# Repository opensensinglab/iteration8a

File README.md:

# iteration8a
iteration8a (in progress)

This is a random collection of in-progress design files and example code (written by myself or others) supporting Iteration 8a.  It's not intended for public use, but only to support my own development efforts.  Materials are not packaged for release, and any use is entirely at your own risk.

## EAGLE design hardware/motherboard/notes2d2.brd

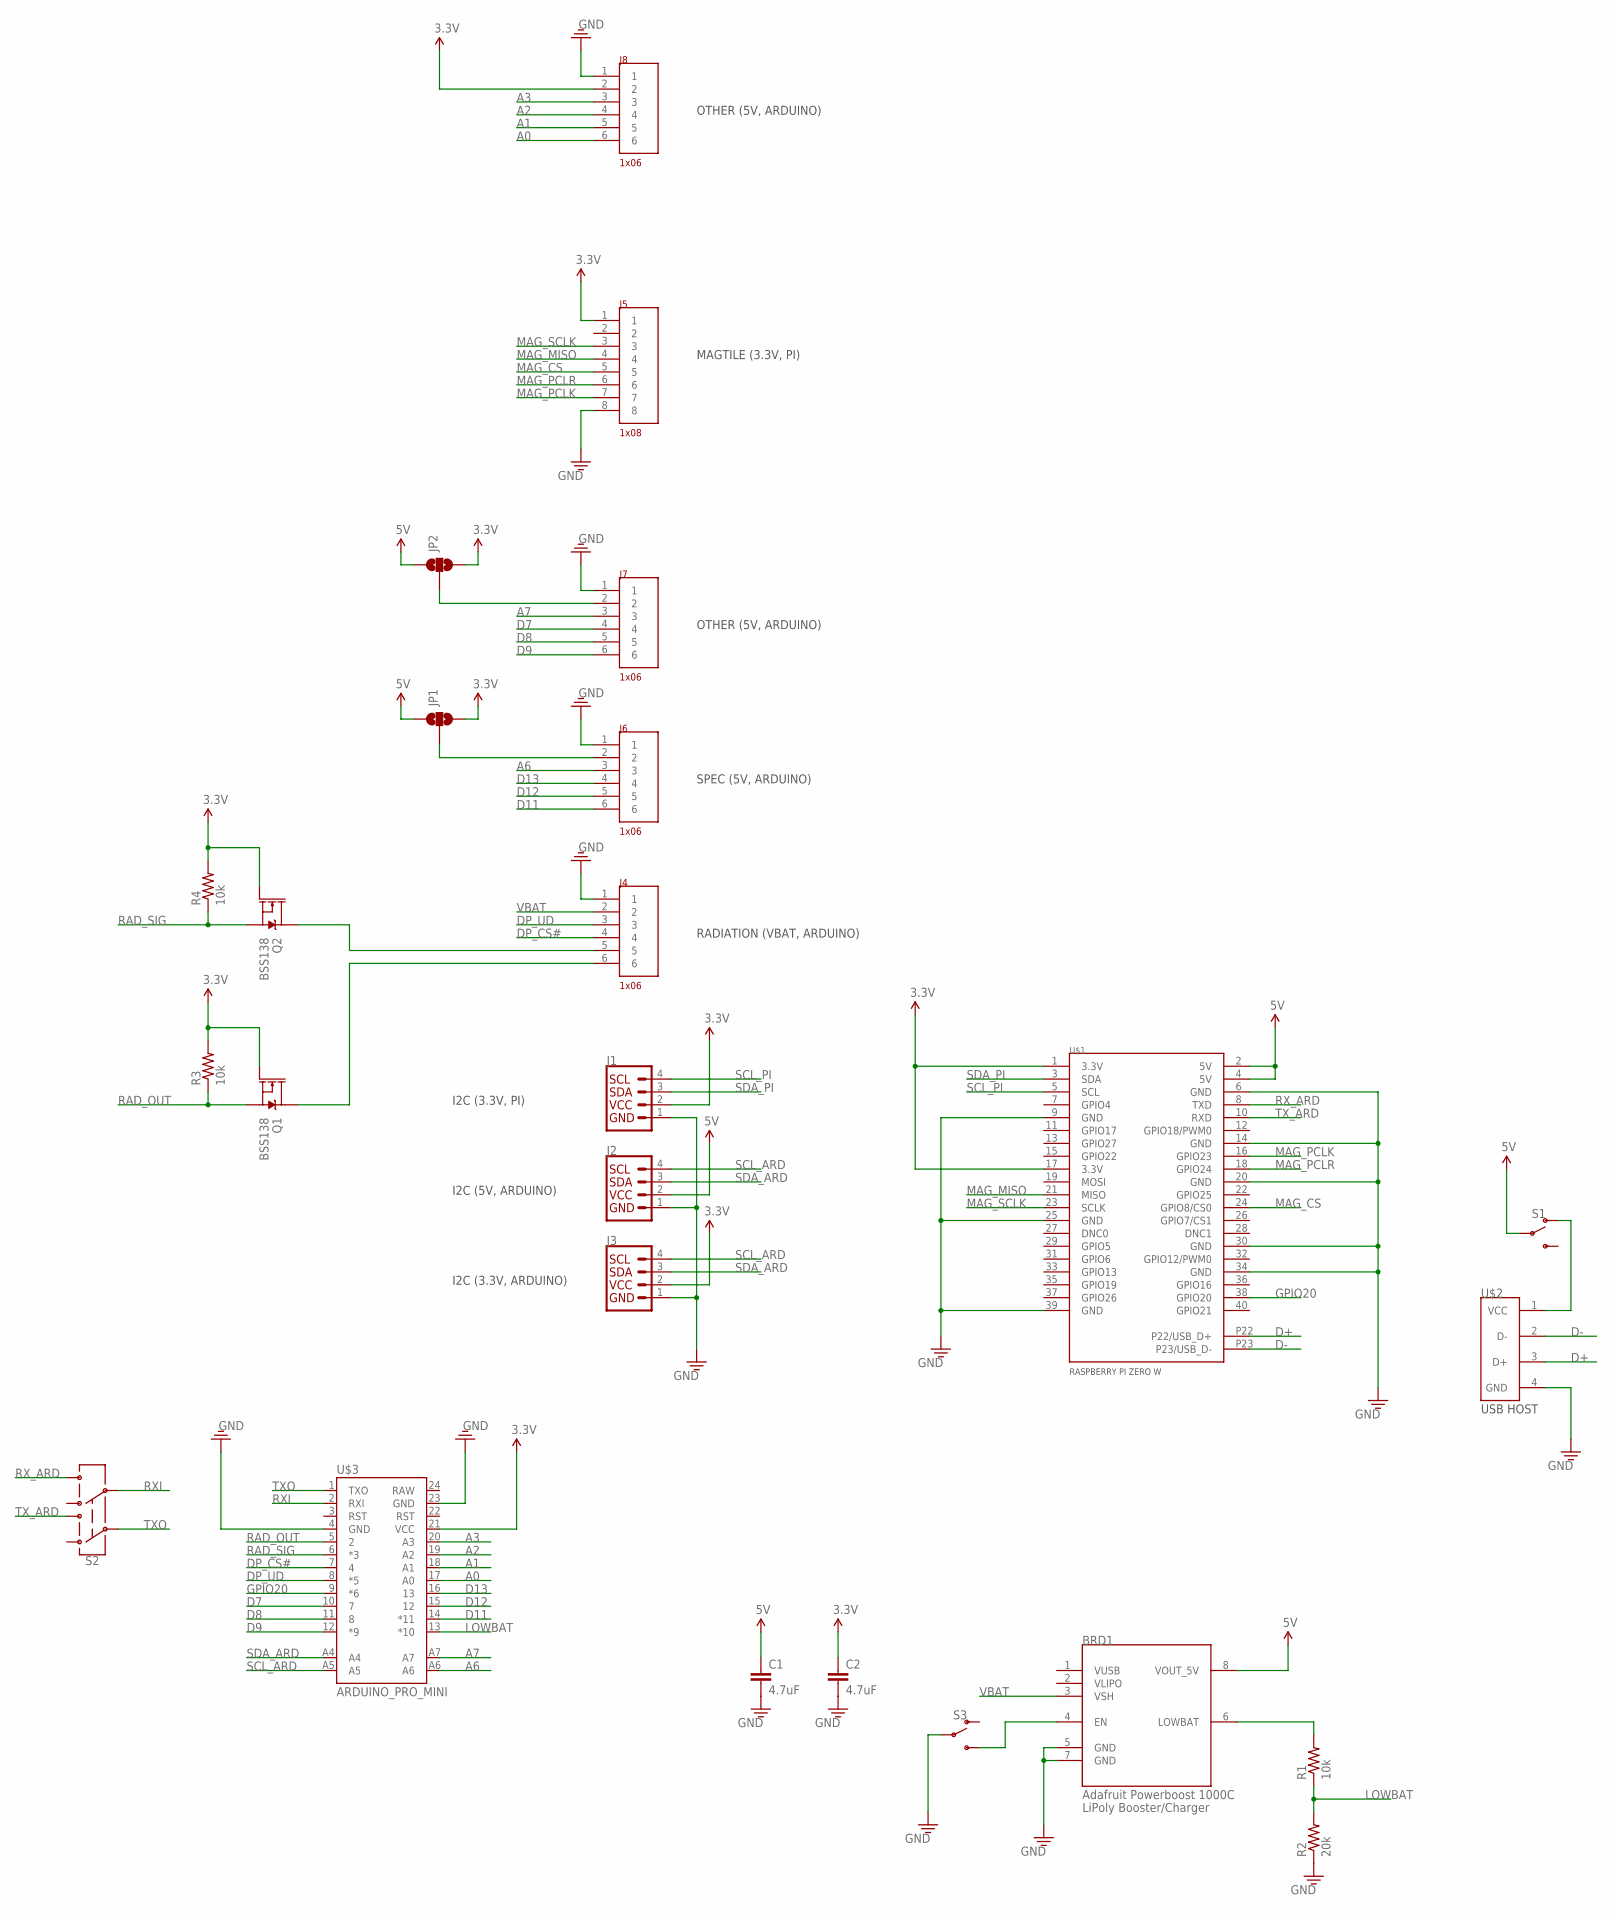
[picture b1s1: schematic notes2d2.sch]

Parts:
BRD1: ADAFRUIT_POWERBOOST_1000C
C1, C2: 4.7uF; 0603
J1, J2, J3: QWIIC_CONNECTORJS-1MM; 1X04_1MM_RA
J4, J6, J7, J8: 1X06; JST-SM06B-1MM
J5: 1X08; JST-SM08B-1MM
JP1, JP2: JUMPER-SMT_3_NO_SILK; SMT-JUMPER_3_NO_SILK
Q1, Q2: BSS138; SOT23-3
R1, R3, R4: 10k; 0603
R2: 20k; 0603
S1, S3: SWITCH-SPDT-SMD-RIGHT-ANGLE; SWITCH_SPST_SMD_A
S2: SWITCH-DPDT-SMD-AYZ0202; SWITCH_DPDT_SMD_AYZ0202
U$1: RASPBERRY-PI-ZEROW-USB
U$2: USB-HOST; 1-292303-6
U$3: ARDUINO_PRO_MINI

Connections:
3.3V: C2.1, J1.2 (VCC), J3.2 (VCC), J5.1, J8.2, JP1.3, JP2.3, Q1.1 (G), Q2.1 (G), R3.2, R4.2, U$1.1 (3.3V), U$1.17 (3.3V), U$3.21 (VCC)
5V: BRD1.8 (VOUT_5V), C1.1, J2.2 (VCC), JP1.1, JP2.1, S1.2, U$1.2 (5V), U$1.4 (5V)
A0: J8.6, U$3.17 (A0)
A1: J8.5, U$3.18 (A1)
A2: J8.4, U$3.19 (A2)
A3: J8.3, U$3.20 (A3)
A6: J6.3, U$3.A6
A7: J7.3, U$3.A7
D7: J7.4, U$3.10 (7)
D8: J7.5, U$3.11 (8)
D9: J7.6, U$3.12 (*9)
D11: J6.6, U$3.14 (*11)
D12: J6.5, U$3.15 (12)
D13: J6.4, U$3.16 (13)
D+: U$1.P22 (P22/USB_D+), U$2.3 (D+)
D-: U$1.P23 (P23/USB_D-), U$2.2 (D-)
DP_CS#: J4.4, U$3.7 (4)
DP_UD: J4.3, U$3.8 (*5)
GND: BRD1.5 (GND), BRD1.7 (GND), C1.2, C2.2, J1.1 (GND), J2.1 (GND), J3.1 (GND), J4.1, J5.8, J6.1, J7.1, J8.1, R2.1, S3.2, U$1.6 (GND), U$1.9 (GND), U$1.14 (GND), U$1.20 (GND), U$1.25 (GND), U$1.30 (GND), U$1.34 (GND), U$1.39 (GND), U$2.4 (GND), U$3.4 (GND), U$3.23 (GND)
GPIO20: U$1.38 (GPIO20), U$3.9 (*6)
LOWBAT: R1.1, R2.2, U$3.13 (*10)
MAG_CS: J5.5, U$1.24 (GPIO8/CS0)
MAG_MISO: J5.4, U$1.21 (MISO)
MAG_PCLK: J5.7, U$1.16 (GPIO23)
MAG_PCLR: J5.6, U$1.18 (GPIO24)
MAG_SCLK: J5.3, U$1.23 (SCLK)
unnamed: BRD1.4 (EN), S3.3 (S)
unnamed: J7.2, JP2.2
unnamed: J6.2, JP1.2
unnamed: J4.5, Q2.3 (D)
unnamed: J4.6, Q1.3 (D)
unnamed: BRD1.6 (LOWBAT), R1.2
unnamed: S1.1 (O), U$2.1 (VCC)
RAD_OUT: Q1.2 (S), R3.1, U$3.5 (2)
RAD_SIG: Q2.2 (S), R4.1, U$3.6 (*3)
RXI: S2.5, U$3.2 (RXI)
RX_ARD: S2.6, U$1.8 (TXD)
SCL_ARD: J2.4 (SCL), J3.4 (SCL), U$3.A5
SCL_PI: J1.4 (SCL), U$1.5 (SCL)
SDA_ARD: J2.3 (SDA), J3.3 (SDA), U$3.A4
SDA_PI: J1.3 (SDA), U$1.3 (SDA)
TXO: S2.2, U$3.1 (TXO)
TX_ARD: S2.3, U$1.10 (RXD)
VBAT: BRD1.3 (VSH), J4.2

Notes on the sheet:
I2C (3.3V, ARDUINO)
I2C (5V, ARDUINO)
I2C (3.3V, PI)
RADIATION (VBAT, ARDUINO)
SPEC (5V, ARDUINO)
OTHER (5V, ARDUINO)
MAGTILE (3.3V, PI)

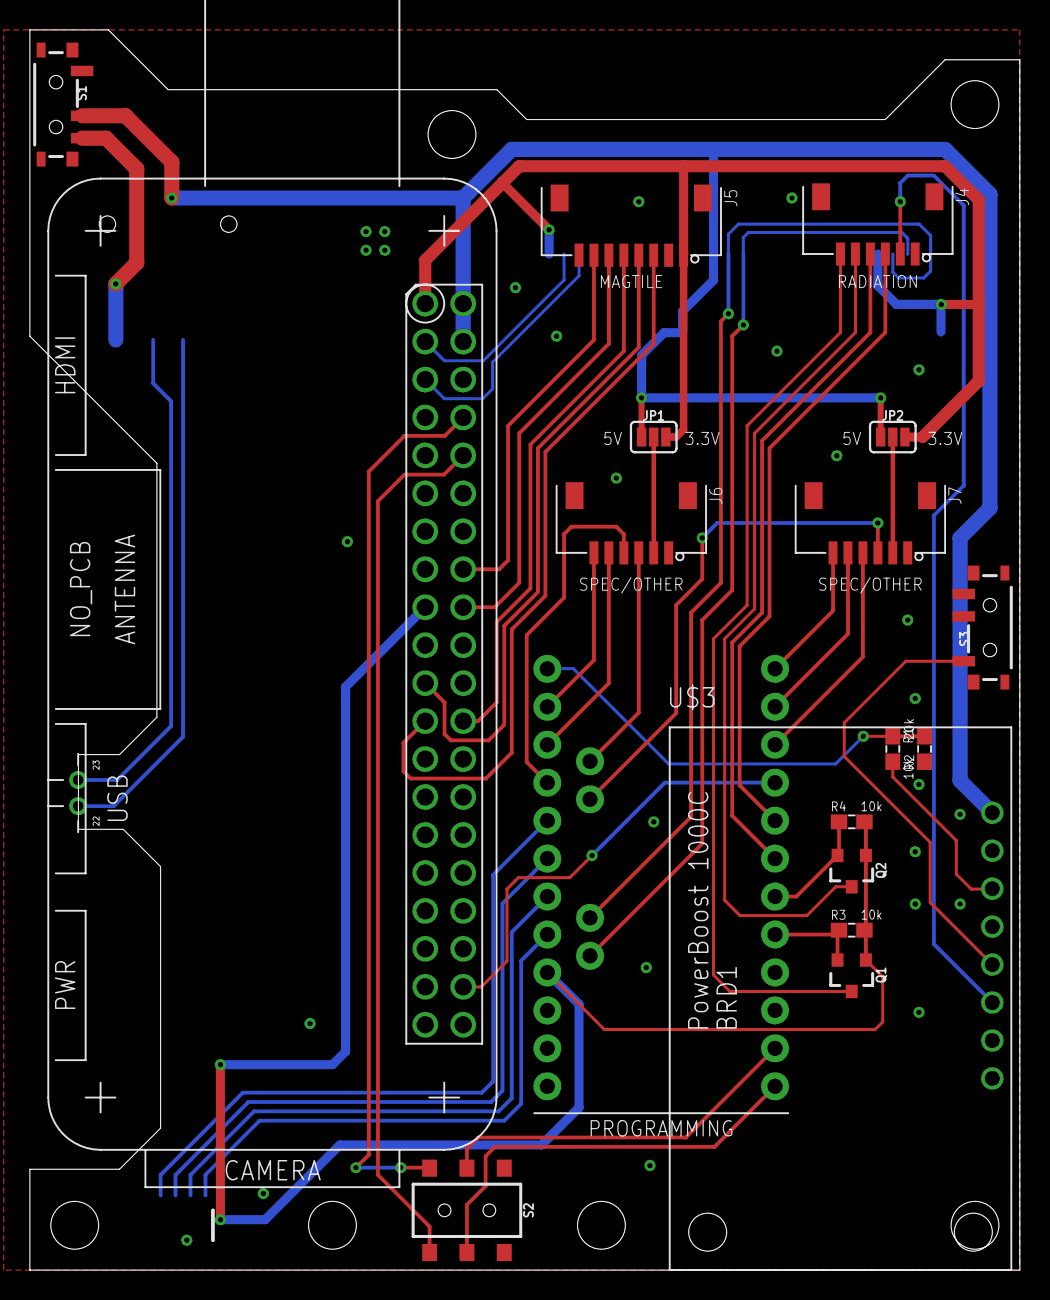
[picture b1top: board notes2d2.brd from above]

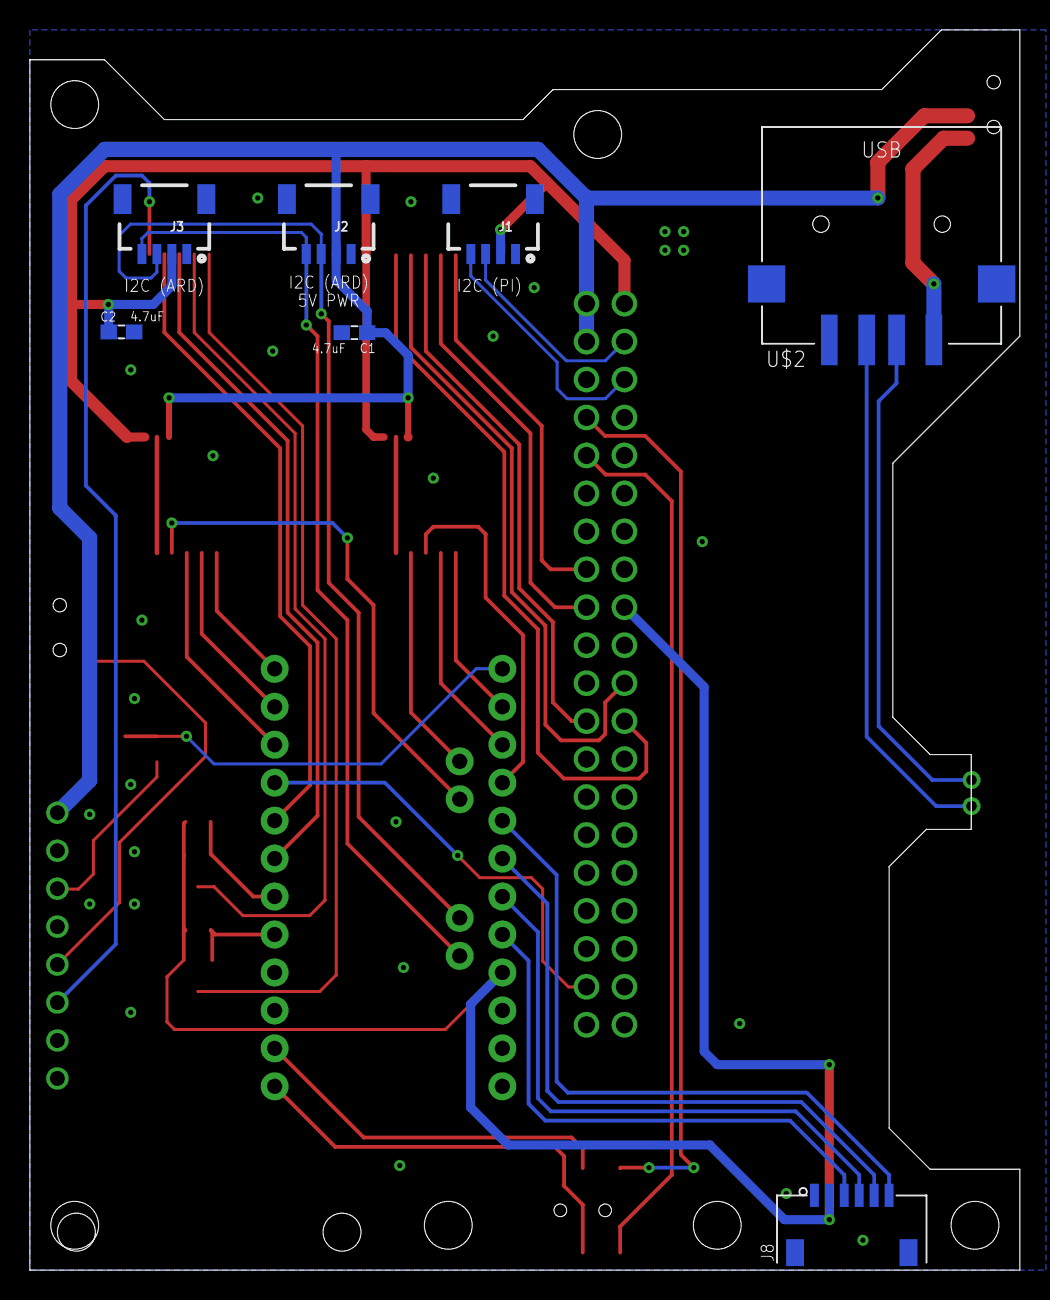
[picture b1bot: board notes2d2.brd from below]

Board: 2 copper layers, 66.2 x 83.0 mm, 25 parts (7 on the bottom side), 44 nets.

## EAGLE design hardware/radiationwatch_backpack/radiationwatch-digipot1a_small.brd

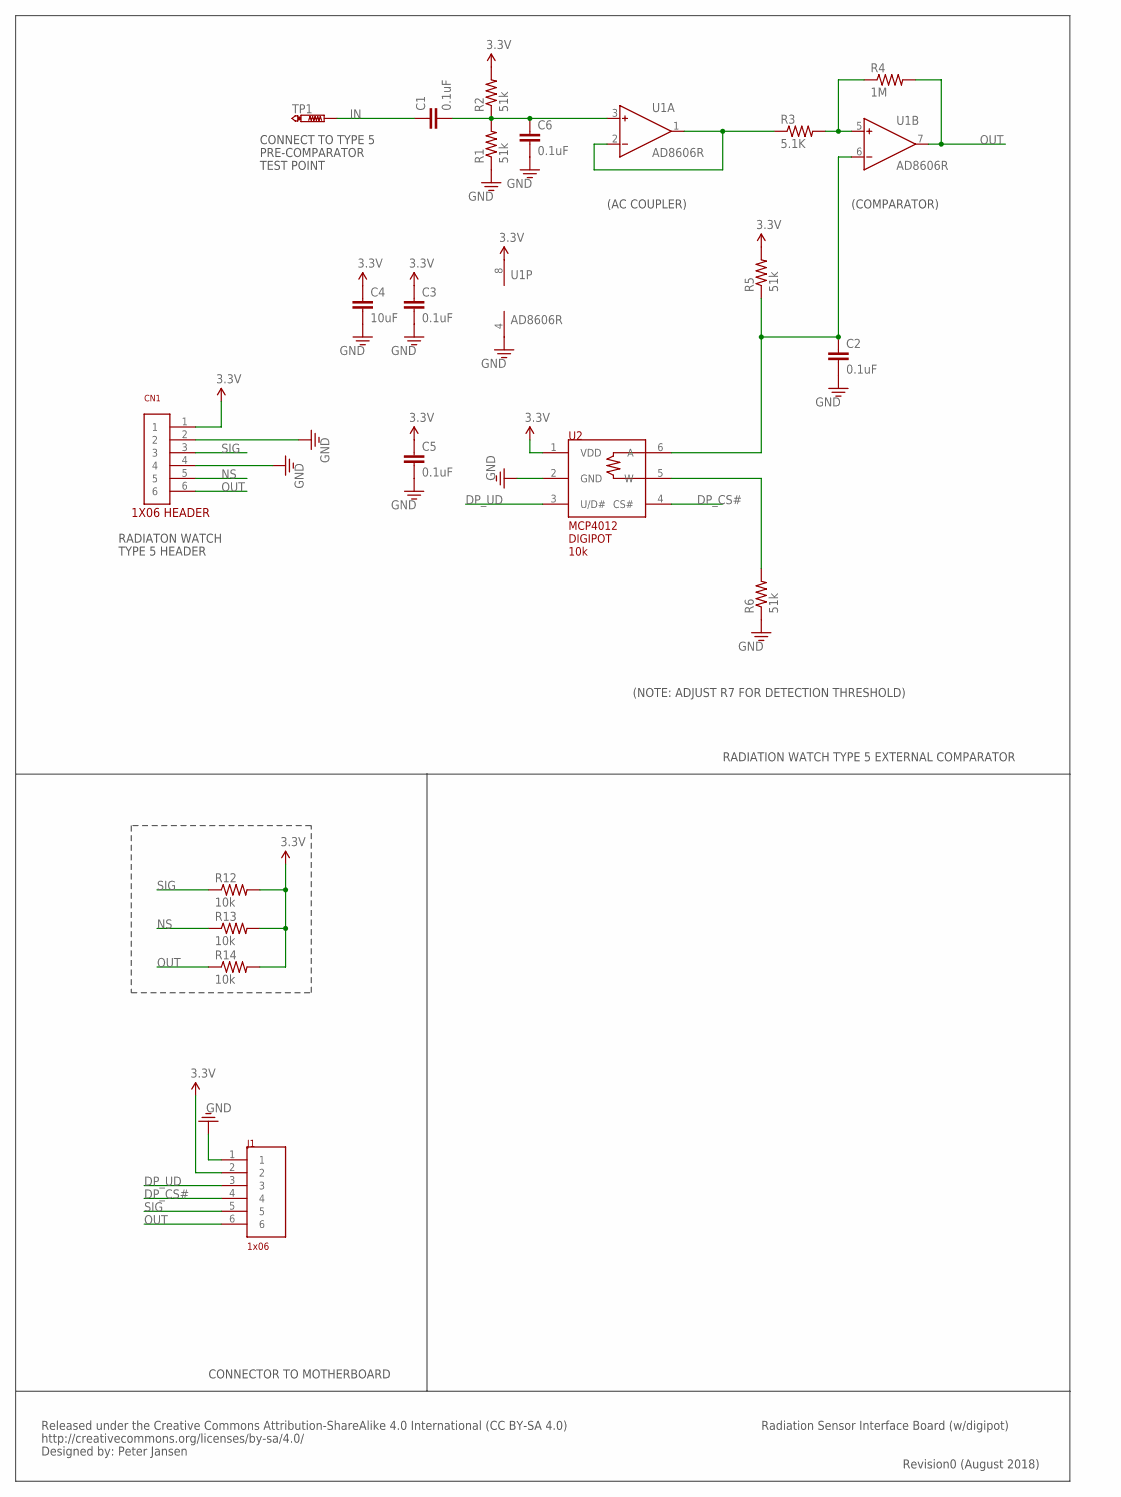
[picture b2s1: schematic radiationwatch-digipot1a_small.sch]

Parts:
C1, C2, C3, C5, C6: 0.1uF; 0603
C4: 10uF; 0603
CN1: 1X06
J1: 1X06; JST-SM06B-1MM
R1, R2, R5, R6: 51k; 0603
R3: 5.1K; 0603
R4: 1M; 0603
R12, R13, R14: 10k; 0603
TP1: PTR1PAD1-13; P1-13
U1: AD8606R; SO8
U2: 10k; SOT-23-6

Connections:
3.3V: C3.1, C4.1, C5.1, CN1.1, J1.2, R2.2, R5.2, R12.2, R13.2, R14.2, U1.8 (V+), U2.1 (VDD)
DP_CS#: J1.4, U2.4 (CS#)
DP_UD: J1.3, U2.3 (U/D#)
GND: C2.2, C3.2, C4.2, C5.2, C6.2, CN1.2, CN1.4, J1.1, R1.1, R6.1, U1.4 (V-), U2.2 (GND)
IN: C1.1, TP1.TP
unnamed: R6.2, U2.5 (W)
unnamed: C1.2, C6.1, R1.2, R2.1, U1.3 (IN+)
unnamed: R3.1, U1.1 (OUT), U1.2 (IN-)
unnamed: R3.2, R4.1, U1.5 (IN+)
unnamed: C2.1, R5.1, U1.6 (IN-), U2.6 (A)
NS: CN1.5, R13.1
OUT: CN1.6, J1.6, R4.2, R14.1, U1.7 (OUT)
SIG: CN1.3, J1.5, R12.1

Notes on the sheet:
(AC COUPLER)
(COMPARATOR)
CONNECT TO TYPE 5
PRE-COMPARATOR
TEST POINT
RADIATON WATCH
TYPE 5 HEADER
(NOTE: ADJUST R7 FOR DETECTION THRESHOLD)
Released under the Creative Commons Attribution-ShareAlike 4.0 International (CC BY-SA 4.0)
http://creativecommons.org/licenses/by-sa/4.0/
Designed by: Peter Jansen
Revision0 (August 2018)
Radiation Sensor Interface Board (w/digipot)
CONNECTOR TO MOTHERBOARD
RADIATION WATCH TYPE 5 EXTERNAL COMPARATOR

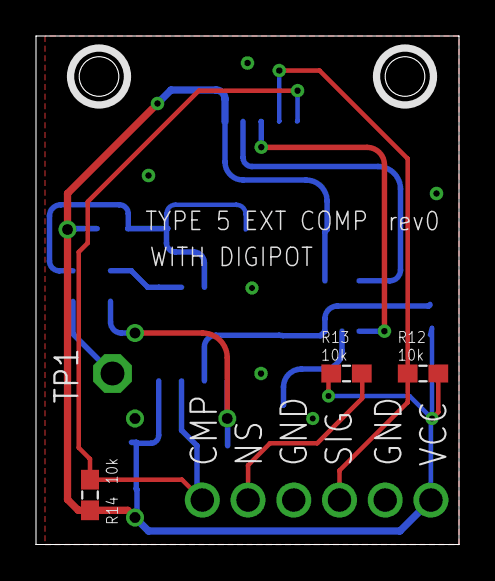
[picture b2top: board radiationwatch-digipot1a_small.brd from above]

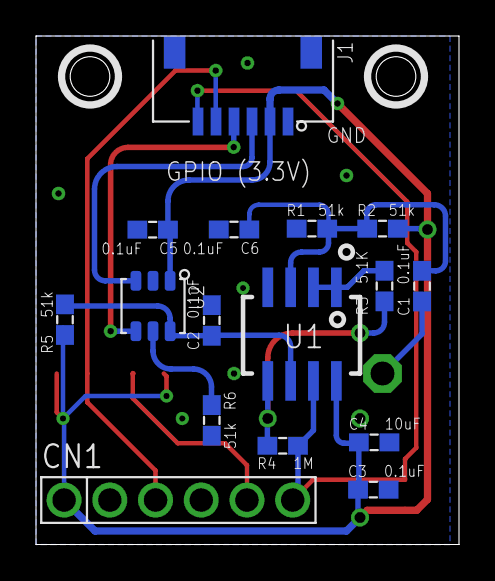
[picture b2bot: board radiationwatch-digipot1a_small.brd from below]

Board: 2 copper layers, 23.5 x 28.2 mm, 20 parts (16 on the bottom side), 13 nets.

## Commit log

2019-09-14 Added initial bits
2019-09-14 Added thermalZero
2019-09-14 Modified string.out to show image as square text image, and report value in C
2019-09-15 modified magtile for motherboard pinout (with wirewrap to correct AOUT/PCLK issue)
2019-09-15 Added additional thermalcamera string test to test timings -- seems very slow
2019-09-15 thermal camera framerate now appears good -- converting to string and writing to console was taking quite a bit of time
2019-09-16 Added initial node test
2019-09-16 Added command line version of readmagtile
2019-09-16 First working demo of magnetic image data being served over node server
2019-09-20 Adding first pass at sending thermal image through json
2019-09-20 Thermal camera interface working -- sends data from python to node.js server
2019-09-21 Added bare Arduino examples
2019-09-21 minor changes
2019-09-21 Added scaffold javascript/html for co2, radiation, and air particle sensors
2019-10-30 Bump bootstrap from 3.3.7 to 3.4.1 in /software/pi/nodetest
    Bumps [bootstrap](https://github.com/twbs/bootstrap) from 3.3.7 to 3.4.1.
    - [Release notes](https://github.com/twbs/bootstrap/releases)
    - [Commits](https://github.com/twbs/bootstrap/compare/v3.3.7...v3.4.1)

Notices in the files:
parts and their libraries:
SparkFun-Connectors: Licensing: Creative Commons ShareAlike 4.0 International - https://creativecommons.org/licenses/by-sa/4.0
